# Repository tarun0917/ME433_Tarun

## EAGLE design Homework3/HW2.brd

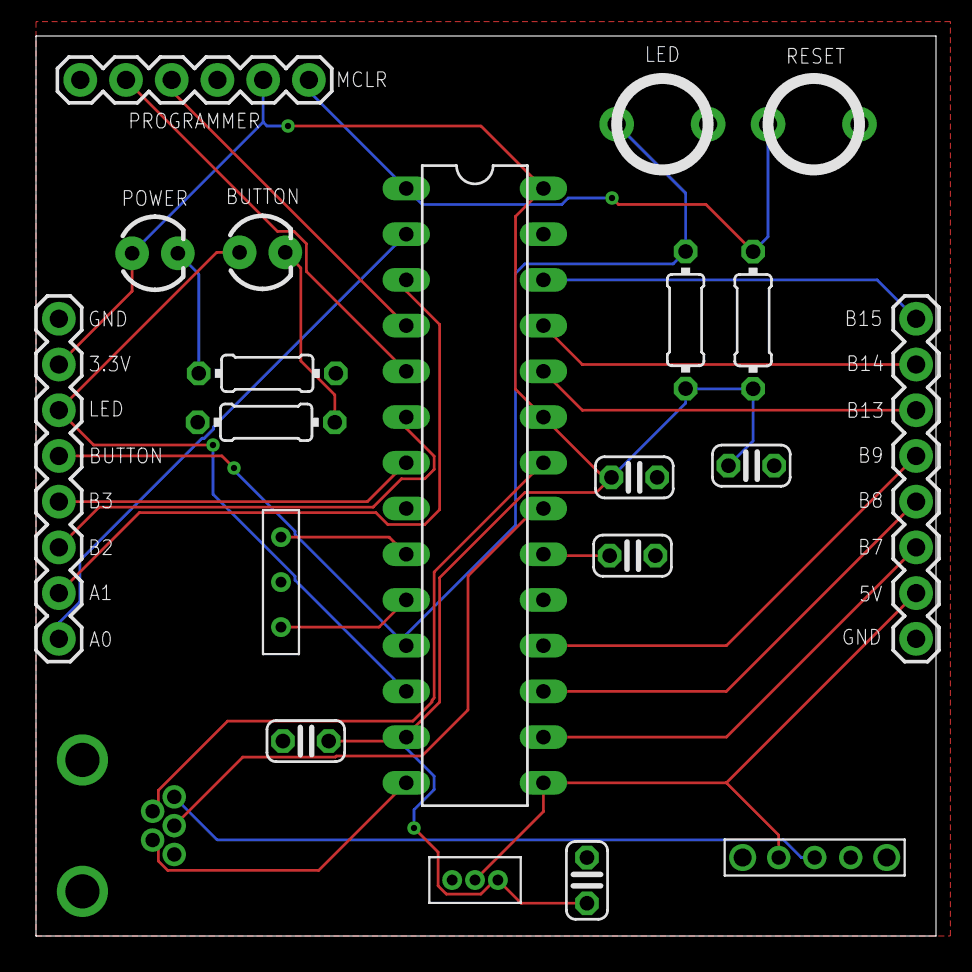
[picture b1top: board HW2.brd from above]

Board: 2 copper layers, 50.0 x 50.0 mm, 21 parts (0 on the bottom side), 27 nets.

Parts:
C1, C2, C3, C4: 10uF; C025-024X044
C5: 0.1uF; C025-024X044
D1, D2: LED_3MM
J1: 1X06
J2, J4: 1X08
J6: USB-MB-H
R1, R4: 330; 0204/7
R2, R3: 10k; 0204/7
U$1: PIC32MX250F128B; DIL28-3
U$2, U$3: SWITCH_BTN_NO; BTN_2
U$4: RESONATOR; 1X3
U$5: VREG3_3V; 1X3_VREG
U$6: SLIDESWITCH; SWITCH

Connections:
3.3V: C1.2, C3.2, C4.1, C5.1, D1.A, J1.2, J2.7, R2.1, R3.1, U$1.13, U$1.23, U$1.28, U$5.VOUT
5V: J4.2, U$1.15, U$5.VIN, U$6.1
!MCLR: J1.1, R3.2, U$1.1, U$3.P$1
A0: J2.1, U$1.2
A1: J2.2, U$1.3
B2: J2.3, U$1.6
B3: J2.4, U$1.7
B7: J4.3, U$1.16
B8: J4.4, U$1.17
B9: J4.5, U$1.18
B13: J4.6, U$1.24
B14: J4.7, U$1.25
B15: J4.8, U$1.26
BUTTON1: J2.5, R2.2, U$1.11, U$2.P$1
D+: J6.D+, U$1.21
D-: J6.D-, U$1.22
GND: C1.1, C2.2, C3.1, C4.2, C5.2, J1.3, J2.8, J4.1, J6.GND, R1.2, R4.2, U$1.8, U$1.19, U$1.27, U$2.P$2, U$3.P$2, U$4.GND, U$5.GND
ID: J6.ID, U$1.14
LED1: D2.A, J2.6, U$1.12
unnamed: D1.K, R4.1
unnamed: C2.1, U$1.20
unnamed: D2.K, R1.1
OSC1: U$1.9, U$4.OSC1
OSC2: U$1.10, U$4.OSC2
PGEC1: J1.5, U$1.5
PGED1: J1.4, U$1.4
VBUSUSB: J6.VBUS, U$6.2

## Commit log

2018-04-09 Version 1
2018-04-10 Version 2
2018-04-17 Second Commit
2018-04-17 Third Commit
2018-05-01 Initital Commit
2018-05-02 Fourth Commit
2018-05-08 Fifth Commit
2018-05-25 Insignificant Changes
2018-06-14 FInal Project
2018-06-14 Added Images

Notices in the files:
parts and their libraries:
SparkFun-LED: Licensing: Creative Commons ShareAlike 4.0 International - https://creativecommons.org/licenses/by-sa/4.0
